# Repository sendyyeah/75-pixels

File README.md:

# 75-pixels
 60% size 75 keys ortholinear

## License

This design may be reproduced, modified, and manufactured for **Personal Use Only** and not for **Public Sale**, however I allow to anyone who want to do small GB for their community for maximum of 10 pieces of this PCB per group buy.

)

This work is licensed under a [Creative Commons Attribution-NonCommercial 4.0 International License](http://creativecommons.org/licenses/by-nc/4.0/).

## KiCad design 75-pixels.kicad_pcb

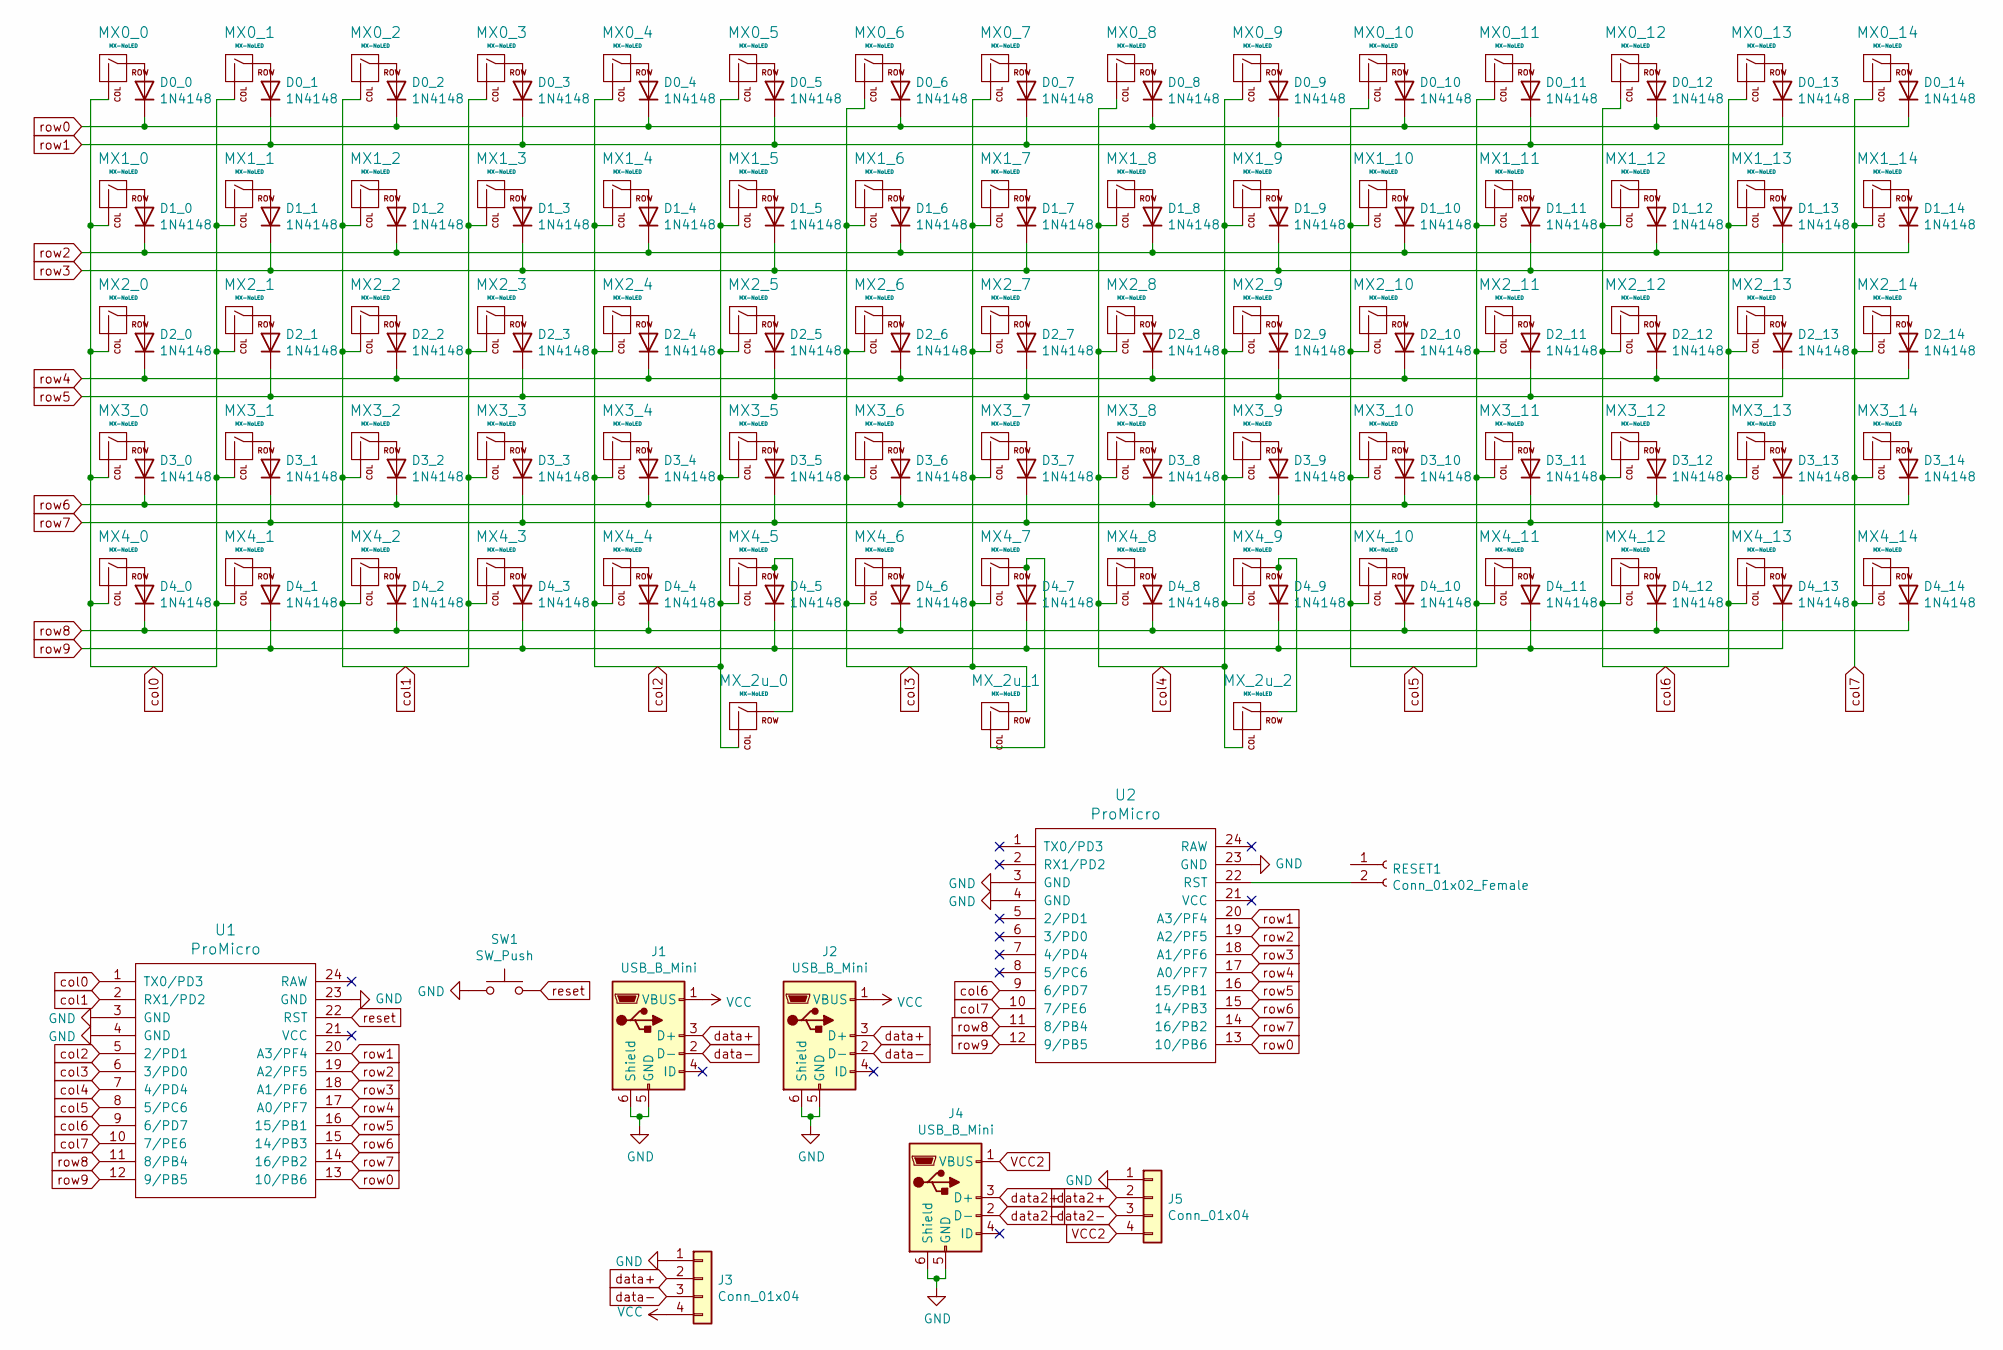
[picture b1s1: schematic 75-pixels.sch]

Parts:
D0_0, D0_1, D0_2, D0_3, D0_4, D0_5, D0_6, D0_7, D0_8, D0_9, D0_10, D0_11, D0_12, D0_13, D0_14, D1_0, D1_1, D1_2, D1_3, D1_4, D1_5, D1_6, D1_7, D1_8, D1_9, D1_10, D1_11, D1_12, D1_13, D1_14, D2_0, D2_1, D2_2, D2_3, D2_4, D2_5, D2_6, D2_7, D2_8, D2_9, D2_10, D2_11, D2_12, D2_13, D2_14, D3_0, D3_1, D3_2, D3_3, D3_4, D3_5, D3_6, D3_7, D3_8, D3_9, D3_10, D3_11, D3_12, D3_13, D3_14, D4_0, D4_1, D4_2, D4_3, D4_4, D4_5, D4_6, D4_7, D4_8, D4_9, D4_10, D4_11, D4_12, D4_13, D4_14: 1N4148; Diode-Hybrid-Back
J1, J2, J4: USB_B_Mini; USB-Mini-B_ LCSC-C46398
J3, J5: Conn_01x04; PinSocket_1x04_P2.00mm_Vertical
MX0_0, MX0_1, MX0_2, MX0_3, MX0_4, MX0_5, MX0_6, MX0_7, MX0_8, MX0_9, MX0_10, MX0_11, MX0_12, MX0_13, MX0_14, MX1_0, MX1_1, MX1_2, MX1_3, MX1_4, MX1_5, MX1_6, MX1_7, MX1_8, MX1_9, MX1_10, MX1_11, MX1_12, MX1_13, MX1_14, MX2_0, MX2_1, MX2_2, MX2_3, MX2_4, MX2_5, MX2_6, MX2_7, MX2_8, MX2_9, MX2_10, MX2_11, MX2_12, MX2_13, MX2_14, MX3_0, MX3_1, MX3_2, MX3_3, MX3_4, MX3_5, MX3_6, MX3_7, MX3_8, MX3_9, MX3_10, MX3_11, MX3_12, MX3_13, MX3_14, MX4_0, MX4_1, MX4_2, MX4_3, MX4_4, MX4_5, MX4_6, MX4_7, MX4_8, MX4_9, MX4_10, MX4_11, MX4_12, MX4_13, MX4_14: MX-NoLED; MX-Alps-Choc-1U-NoLED
MX_2u_0, MX_2u_1, MX_2u_2: MX-NoLED; MXOnly-2U-ReversedStabilizers-NoLED
RESET1: Conn_01x02_Female; PinHeader_2x01_P2.00mm_Vertical
SW1: SW_Push; SW_SPST_TL3342
U1, U2: ProMicro; ArduinoProMicro-BackSide

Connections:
GND: J1.5 (GND), J1.6 (Shield), J2.5 (GND), J2.6 (Shield), J3.1, J4.5 (GND), J4.6 (Shield), J5.1, SW1.1, U1.3 (GND), U1.4 (GND), U1.23 (GND), U2.3 (GND), U2.4 (GND), U2.23 (GND)
unnamed: D0_0.2 (A), MX0_0.1 (COL)
unnamed: D0_1.2 (A), MX0_1.1 (COL)
unnamed: D0_2.2 (A), MX0_2.1 (COL)
unnamed: D0_3.2 (A), MX0_3.1 (COL)
unnamed: D0_4.2 (A), MX0_4.1 (COL)
unnamed: D0_5.2 (A), MX0_5.1 (COL)
unnamed: D0_6.2 (A), MX0_6.1 (COL)
unnamed: D0_7.2 (A), MX0_7.1 (COL)
unnamed: D0_8.2 (A), MX0_8.1 (COL)
unnamed: D0_9.2 (A), MX0_9.1 (COL)
unnamed: D0_10.2 (A), MX0_10.1 (COL)
unnamed: D0_11.2 (A), MX0_11.1 (COL)
unnamed: D0_12.2 (A), MX0_12.1 (COL)
unnamed: D0_13.2 (A), MX0_13.1 (COL)
unnamed: D0_14.2 (A), MX0_14.1 (COL)
unnamed: D1_0.2 (A), MX1_0.1 (COL)
unnamed: D1_1.2 (A), MX1_1.1 (COL)
unnamed: D1_2.2 (A), MX1_2.1 (COL)
unnamed: D1_3.2 (A), MX1_3.1 (COL)
unnamed: D1_4.2 (A), MX1_4.1 (COL)
unnamed: D1_5.2 (A), MX1_5.1 (COL)
unnamed: D1_6.2 (A), MX1_6.1 (COL)
unnamed: D1_7.2 (A), MX1_7.1 (COL)
unnamed: D1_8.2 (A), MX1_8.1 (COL)
unnamed: D1_9.2 (A), MX1_9.1 (COL)
unnamed: D1_10.2 (A), MX1_10.1 (COL)
unnamed: D1_11.2 (A), MX1_11.1 (COL)
unnamed: D1_12.2 (A), MX1_12.1 (COL)
unnamed: D1_13.2 (A), MX1_13.1 (COL)
unnamed: D1_14.2 (A), MX1_14.1 (COL)
unnamed: D2_0.2 (A), MX2_0.1 (COL)
unnamed: D2_1.2 (A), MX2_1.1 (COL)
unnamed: D2_2.2 (A), MX2_2.1 (COL)
unnamed: D2_3.2 (A), MX2_3.1 (COL)
unnamed: D2_4.2 (A), MX2_4.1 (COL)
unnamed: D2_5.2 (A), MX2_5.1 (COL)
unnamed: D2_6.2 (A), MX2_6.1 (COL)
unnamed: D2_7.2 (A), MX2_7.1 (COL)
unnamed: D2_8.2 (A), MX2_8.1 (COL)
unnamed: D2_9.2 (A), MX2_9.1 (COL)
unnamed: D2_10.2 (A), MX2_10.1 (COL)
unnamed: D2_11.2 (A), MX2_11.1 (COL)
unnamed: D2_12.2 (A), MX2_12.1 (COL)
unnamed: D2_13.2 (A), MX2_13.1 (COL)
unnamed: D2_14.2 (A), MX2_14.1 (COL)
unnamed: D3_0.2 (A), MX3_0.1 (COL)
unnamed: D3_1.2 (A), MX3_1.1 (COL)
unnamed: D3_2.2 (A), MX3_2.1 (COL)
unnamed: D3_3.2 (A), MX3_3.1 (COL)
unnamed: D3_4.2 (A), MX3_4.1 (COL)
unnamed: D3_5.2 (A), MX3_5.1 (COL)
unnamed: D3_6.2 (A), MX3_6.1 (COL)
unnamed: D3_7.2 (A), MX3_7.1 (COL)
unnamed: D3_8.2 (A), MX3_8.1 (COL)
unnamed: D3_9.2 (A), MX3_9.1 (COL)
unnamed: D3_10.2 (A), MX3_10.1 (COL)
unnamed: D3_11.2 (A), MX3_11.1 (COL)
unnamed: D3_12.2 (A), MX3_12.1 (COL)
unnamed: D3_13.2 (A), MX3_13.1 (COL)
unnamed: D3_14.2 (A), MX3_14.1 (COL)
unnamed: D4_0.2 (A), MX4_0.1 (COL)
unnamed: D4_1.2 (A), MX4_1.1 (COL)
unnamed: D4_2.2 (A), MX4_2.1 (COL)
unnamed: D4_3.2 (A), MX4_3.1 (COL)
unnamed: D4_4.2 (A), MX4_4.1 (COL)
unnamed: D4_5.2 (A), MX4_5.1 (COL), MX_2u_0.1 (COL)
unnamed: D4_6.2 (A), MX4_6.1 (COL)
unnamed: D4_7.2 (A), MX4_7.1 (COL), MX_2u_1.2 (ROW)
unnamed: D4_8.2 (A), MX4_8.1 (COL)
unnamed: D4_9.2 (A), MX4_9.1 (COL), MX_2u_2.1 (COL)
unnamed: D4_10.2 (A), MX4_10.1 (COL)
unnamed: D4_11.2 (A), MX4_11.1 (COL)
unnamed: D4_12.2 (A), MX4_12.1 (COL)
unnamed: D4_13.2 (A), MX4_13.1 (COL)
unnamed: D4_14.2 (A), MX4_14.1 (COL)
unnamed: RESET1.2, U2.22 (RST)
VCC: J1.1 (VBUS), J2.1 (VBUS), J3.4
VCC2: J4.1 (VBUS), J5.4
col0: MX0_0.2 (ROW), MX0_1.2 (ROW), MX1_0.2 (ROW), MX1_1.2 (ROW), MX2_0.2 (ROW), MX2_1.2 (ROW), MX3_0.2 (ROW), MX3_1.2 (ROW), MX4_0.2 (ROW), MX4_1.2 (ROW), U1.1 (TX0/PD3)
col1: MX0_2.2 (ROW), MX0_3.2 (ROW), MX1_2.2 (ROW), MX1_3.2 (ROW), MX2_2.2 (ROW), MX2_3.2 (ROW), MX3_2.2 (ROW), MX3_3.2 (ROW), MX4_2.2 (ROW), MX4_3.2 (ROW), U1.2 (RX1/PD2)
col2: MX0_4.2 (ROW), MX0_5.2 (ROW), MX1_4.2 (ROW), MX1_5.2 (ROW), MX2_4.2 (ROW), MX2_5.2 (ROW), MX3_4.2 (ROW), MX3_5.2 (ROW), MX4_4.2 (ROW), MX4_5.2 (ROW), MX_2u_0.2 (ROW), U1.5 (2/PD1)
col3: MX0_6.2 (ROW), MX0_7.2 (ROW), MX1_6.2 (ROW), MX1_7.2 (ROW), MX2_6.2 (ROW), MX2_7.2 (ROW), MX3_6.2 (ROW), MX3_7.2 (ROW), MX4_6.2 (ROW), MX4_7.2 (ROW), MX_2u_1.1 (COL), U1.6 (3/PD0)
col4: MX0_8.2 (ROW), MX0_9.2 (ROW), MX1_8.2 (ROW), MX1_9.2 (ROW), MX2_8.2 (ROW), MX2_9.2 (ROW), MX3_8.2 (ROW), MX3_9.2 (ROW), MX4_8.2 (ROW), MX4_9.2 (ROW), MX_2u_2.2 (ROW), U1.7 (4/PD4)
col5: MX0_10.2 (ROW), MX0_11.2 (ROW), MX1_10.2 (ROW), MX1_11.2 (ROW), MX2_10.2 (ROW), MX2_11.2 (ROW), MX3_10.2 (ROW), MX3_11.2 (ROW), MX4_10.2 (ROW), MX4_11.2 (ROW), U1.8 (5/PC6)
col6: MX0_12.2 (ROW), MX0_13.2 (ROW), MX1_12.2 (ROW), MX1_13.2 (ROW), MX2_12.2 (ROW), MX2_13.2 (ROW), MX3_12.2 (ROW), MX3_13.2 (ROW), MX4_12.2 (ROW), MX4_13.2 (ROW), U1.9 (6/PD7), U2.9 (6/PD7)
col7: MX0_14.2 (ROW), MX1_14.2 (ROW), MX2_14.2 (ROW), MX3_14.2 (ROW), MX4_14.2 (ROW), U1.10 (7/PE6), U2.10 (7/PE6)
data2+: J4.3 (D+), J5.2
data2-: J4.2 (D-), J5.3
data+: J1.3 (D+), J2.3 (D+), J3.2
data-: J1.2 (D-), J2.2 (D-), J3.3
reset: SW1.2, U1.22 (RST)
row0: D0_0.1 (K), D0_2.1 (K), D0_4.1 (K), D0_6.1 (K), D0_8.1 (K), D0_10.1 (K), D0_12.1 (K), D0_14.1 (K), U1.13 (10/PB6), U2.13 (10/PB6)
row1: D0_1.1 (K), D0_3.1 (K), D0_5.1 (K), D0_7.1 (K), D0_9.1 (K), D0_11.1 (K), D0_13.1 (K), U1.20 (A3/PF4), U2.20 (A3/PF4)
row2: D1_0.1 (K), D1_2.1 (K), D1_4.1 (K), D1_6.1 (K), D1_8.1 (K), D1_10.1 (K), D1_12.1 (K), D1_14.1 (K), U1.19 (A2/PF5), U2.19 (A2/PF5)
row3: D1_1.1 (K), D1_3.1 (K), D1_5.1 (K), D1_7.1 (K), D1_9.1 (K), D1_11.1 (K), D1_13.1 (K), U1.18 (A1/PF6), U2.18 (A1/PF6)
row4: D2_0.1 (K), D2_2.1 (K), D2_4.1 (K), D2_6.1 (K), D2_8.1 (K), D2_10.1 (K), D2_12.1 (K), D2_14.1 (K), U1.17 (A0/PF7), U2.17 (A0/PF7)
row5: D2_1.1 (K), D2_3.1 (K), D2_5.1 (K), D2_7.1 (K), D2_9.1 (K), D2_11.1 (K), D2_13.1 (K), U1.16 (15/PB1), U2.16 (15/PB1)
row6: D3_0.1 (K), D3_2.1 (K), D3_4.1 (K), D3_6.1 (K), D3_8.1 (K), D3_10.1 (K), D3_12.1 (K), D3_14.1 (K), U1.15 (14/PB3), U2.15 (14/PB3)
row7: D3_1.1 (K), D3_3.1 (K), D3_5.1 (K), D3_7.1 (K), D3_9.1 (K), D3_11.1 (K), D3_13.1 (K), U1.14 (16/PB2), U2.14 (16/PB2)
row8: D4_0.1 (K), D4_2.1 (K), D4_4.1 (K), D4_6.1 (K), D4_8.1 (K), D4_10.1 (K), D4_12.1 (K), D4_14.1 (K), U1.11 (8/PB4), U2.11 (8/PB4)
row9: D4_1.1 (K), D4_3.1 (K), D4_5.1 (K), D4_7.1 (K), D4_9.1 (K), D4_11.1 (K), D4_13.1 (K), U1.12 (9/PB5), U2.12 (9/PB5)

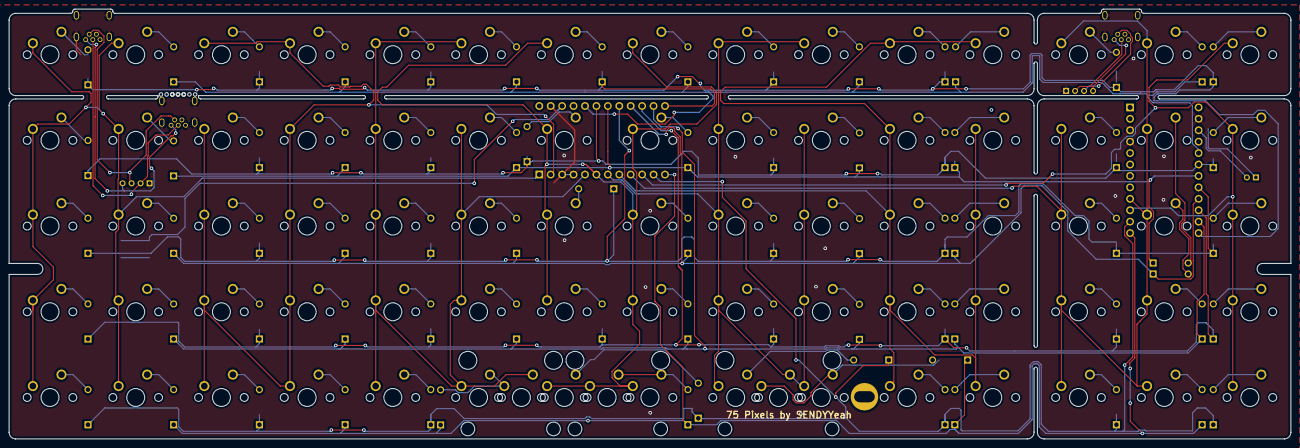
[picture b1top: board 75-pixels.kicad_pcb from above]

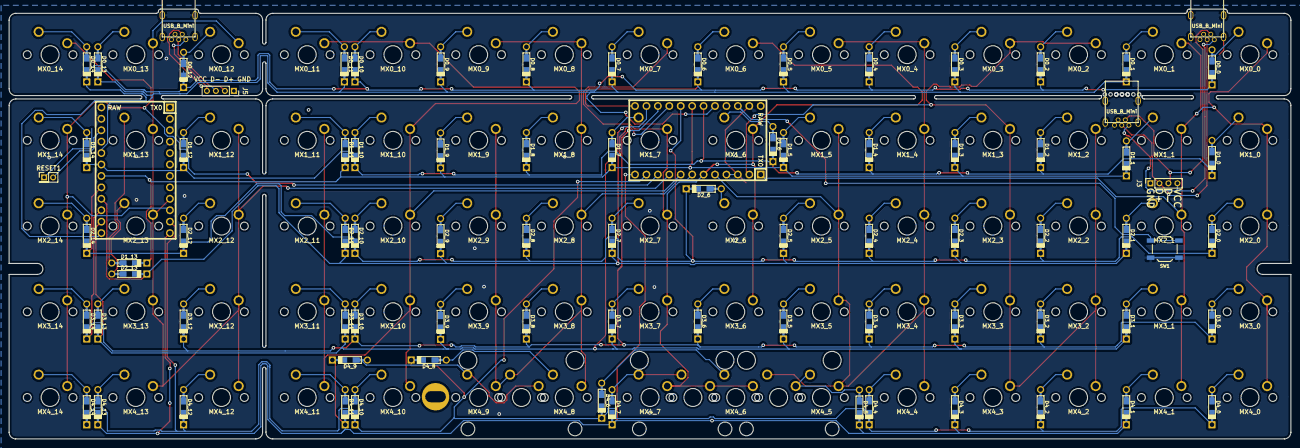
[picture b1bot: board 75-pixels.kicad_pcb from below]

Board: 2 copper layers, 284.9 x 95.5 mm, 163 parts (7 on the bottom side), 102 nets.

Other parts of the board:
Poker_oval_hole: VAL**; Poker_oval_hole

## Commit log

2021-02-07 Update gerbers
2021-03-03 Move diodes
2021-03-12 Update fp-info-cache
